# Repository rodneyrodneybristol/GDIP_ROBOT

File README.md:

# UWE GDIP 2022, GROUP 7D RESISTOR SORTING ROBOT

<b>How to assemble and run</b>
<br>
To install:
<br>
```
git clone https://github.com/rodneyrodneybristol/GDIP_ROBOT
```
<br>
or download the .zip repository directly
<br><br>
Install platform IO, to open the firmware files for the motherboard and ohm meter board. 
<br>
Firmware may take a little while to load and build initially if you do not already have the Pi Pico SDK and Arduino frameworks installed. 
<br>
Firmware can be loaded to the Pi Pico directly and the Atmega328p can be programmed using an AVR programmer or Arduino in ISP programmer mode.
<br><br>
to 3D print the conveoyr belt, simply load the provided STLs in to any chopper software. Best to print them vertically to avoid excessive infil.
<br><br>
2 x 5V supplies, with at least 2A each are required  to run this system, one which handles the mobo/servos/ohm meter etc and another for powering the conveoyrs NEMA17 stepper motor. 
<br><br>
Calibration offset for the Robot can be adjusted in the 
```
startAndCalibrateArm();
``` function within the mobo/mainboard main.cpp file. These will need to be set once when loading the system, in case any servos have serious offsets. This allows for more precise movements of the arm.
<br><br>

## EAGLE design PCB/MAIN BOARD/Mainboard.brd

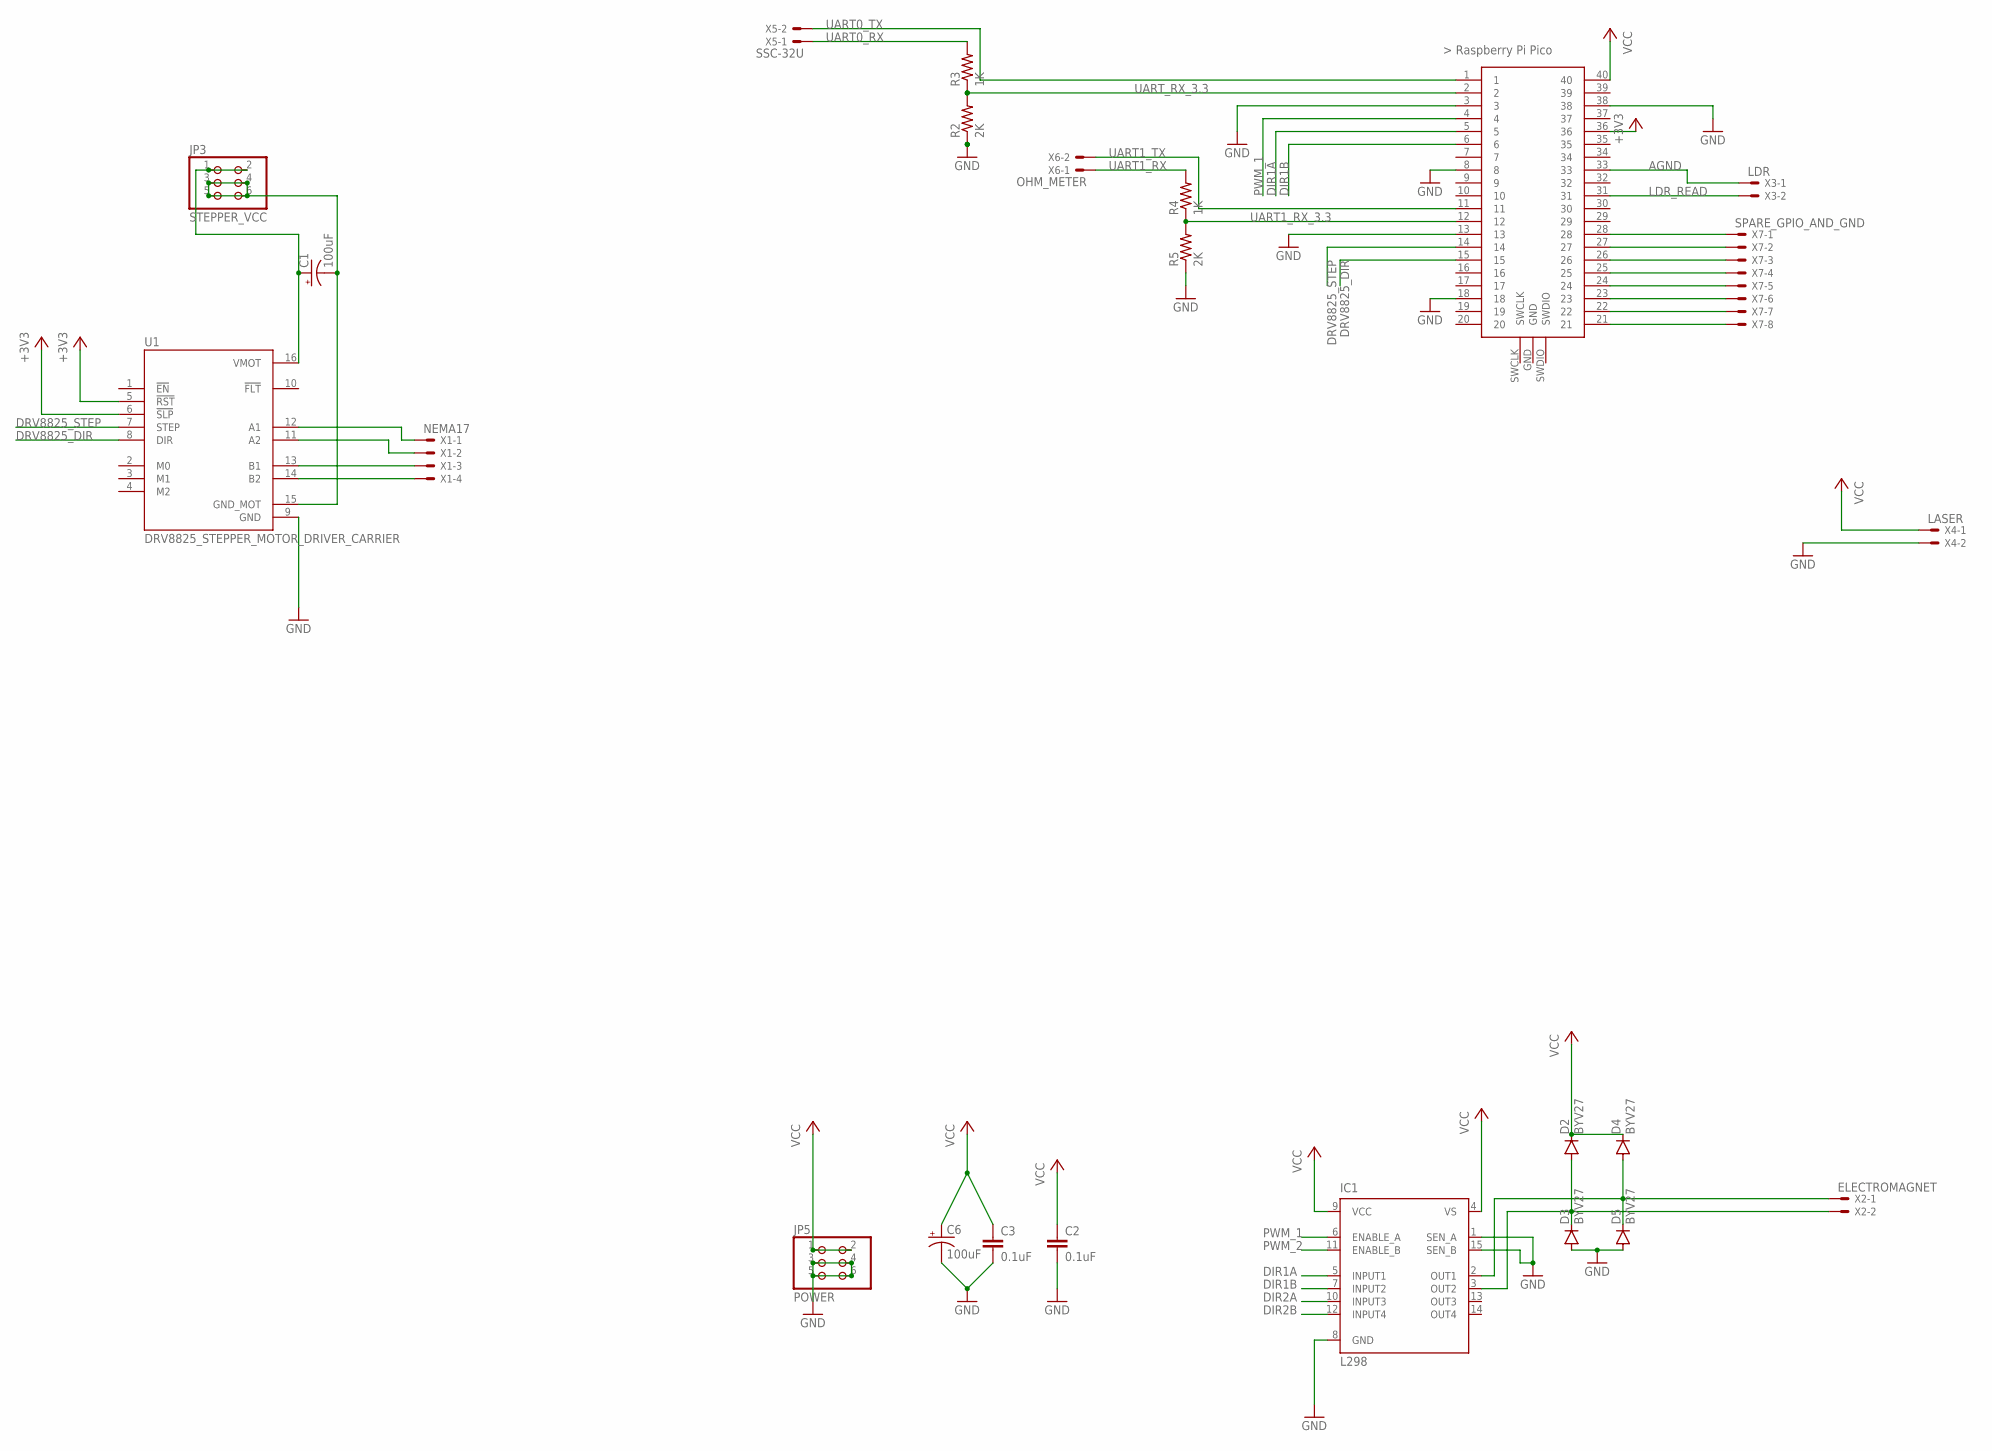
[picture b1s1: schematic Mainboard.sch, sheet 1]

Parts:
C1, C6: 100uF; CPOL-RADIAL-2.5MM-6.5MM
C2, C3: 0.1uF; 0603
D2, D3, D4, D5: BYV27; SOD57-10
IC1: L298; MULTIWATT-15
JP3: STEPPER_VCC; 2X03
JP5: POWER; 2X03
R2, R5: 2K; R0603
R3, R4: 1K; R0603
U1: DRV8825_STEPPER_MOTOR_DRIVER_CARRIER; IC_DRV8825_STEPPER_MOTOR_DRIVER_CARRIER
U$1: RASPBERRY-PI-PICO_W; FT_RASPBERRY-PI-PICO_TH
X1: NEMA17; 22-23-2041
X2: ELECTROMAGNET; 22-23-2021
X3: LDR; 22-23-2021
X4: LASER; 22-23-2021
X5: SSC-32U; 22-23-2021
X6: OHM_METER; 22-23-2021
X7: SPARE_GPIO_AND_GND; 22-23-2081

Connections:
+3V3: U1.5 (!RST), U1.6 (!SLP), U$1.36
+5V: C2.1, IC1.9 (VCC)
AGND: U$1.33, X3.1
DIR1A: IC1.5 (INPUT1), U$1.5
DIR1B: IC1.7 (INPUT2), U$1.6
DIR2A: IC1.10 (INPUT3)
DIR2B: IC1.12 (INPUT4)
DRV8825_DIR: U1.8 (DIR), U$1.15
DRV8825_STEP: U1.7 (STEP), U$1.14
GND: C2.2, C3.2, C6.2 (-), D3.A, D5.A, IC1.1 (SEN_A), IC1.8 (GND), IC1.15 (SEN_B), JP5.3, JP5.4, JP5.5, JP5.6, R2.1, R5.1, U1.9 (GND), U$1.3, U$1.8, U$1.13, U$1.18, U$1.38, X4.2
LDR_READ: U$1.31, X3.2
MOTOR_1_+: D4.A, D5.C, IC1.2 (OUT1), X2.1
MOTOR_1_-: D2.A, D3.C, IC1.3 (OUT2), X2.2
unnamed: C1.1 (+), JP3.1, JP3.2, U1.16 (VMOT)
unnamed: C1.2 (-), JP3.3, JP3.4, JP3.5, JP3.6, U1.15 (GND_MOT)
unnamed: U1.12 (A1), X1.1
unnamed: U1.11 (A2), X1.2
unnamed: U1.13 (B1), X1.3
unnamed: U1.14 (B2), X1.4
unnamed: U$1.21, X7.8
unnamed: U$1.22, X7.7
unnamed: U$1.25, X7.4
unnamed: U$1.23, X7.6
unnamed: U$1.24, X7.5
unnamed: U$1.26, X7.3
unnamed: U$1.27, X7.2
unnamed: U$1.28, X7.1
PWM_1: IC1.6 (ENABLE_A), U$1.4
PWM_2: IC1.11 (ENABLE_B)
UART0_RX: R3.2, X5.1
UART0_TX: U$1.1, X5.2
UART1_RX: R4.2, X6.1
UART1_RX_3.3: R4.1, R5.2, U$1.12
UART1_TX: U$1.11, X6.2
UART_RX_3.3: R2.2, R3.1, U$1.2
VCC: C3.1, C6.1 (+), D2.C, D4.C, IC1.4 (VS), JP5.1, JP5.2, U$1.40, X4.1

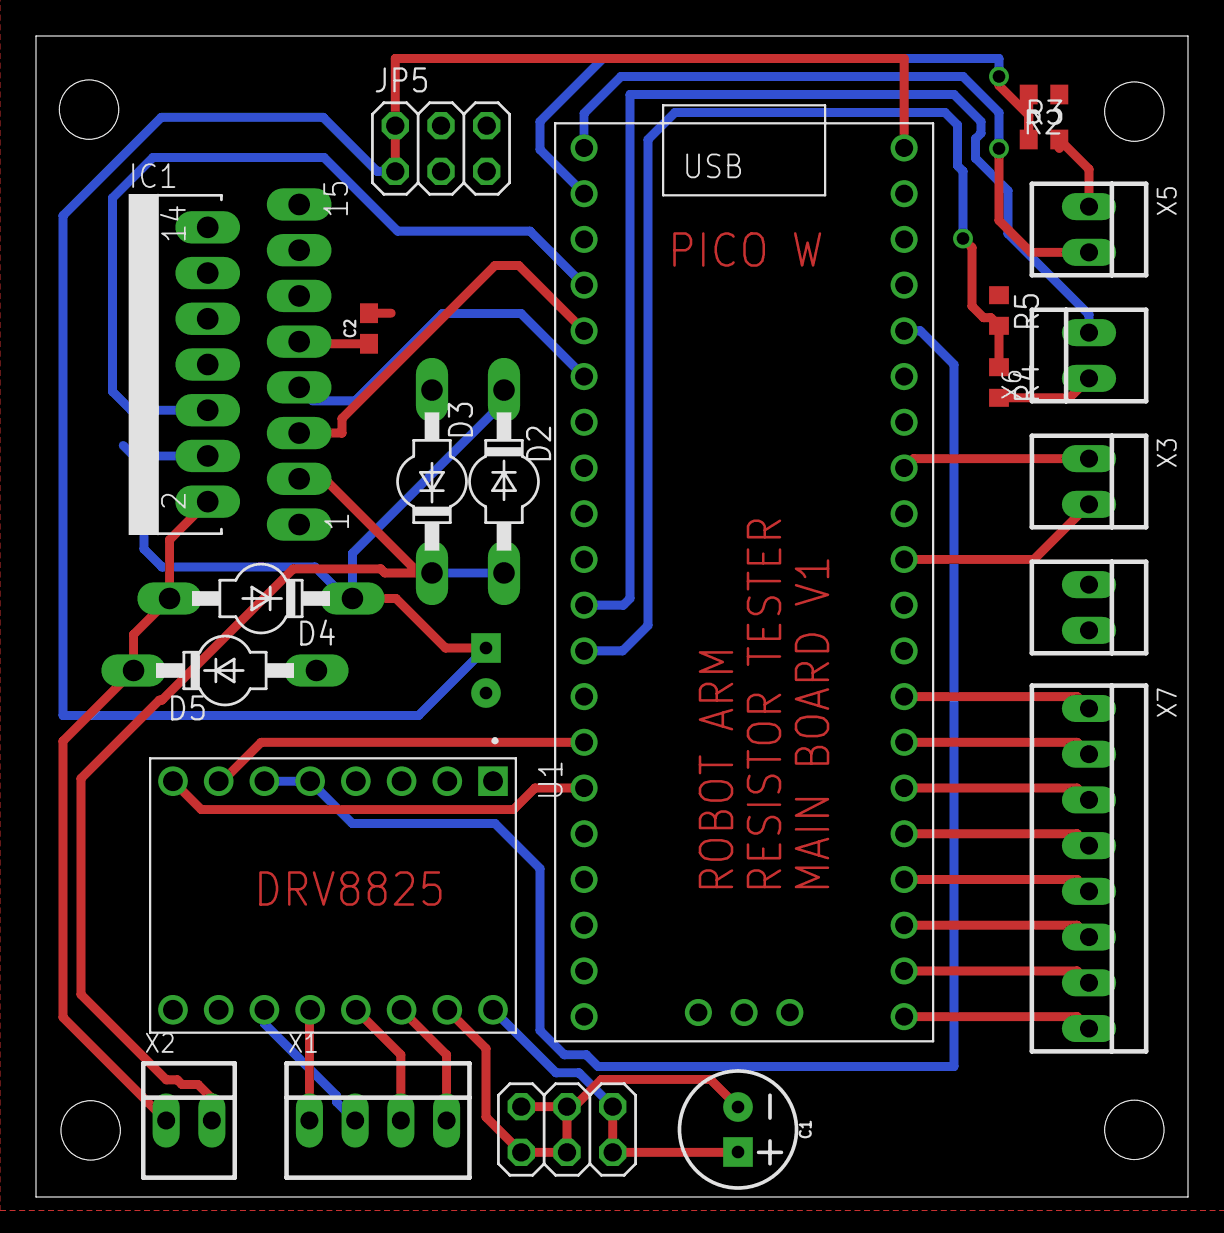
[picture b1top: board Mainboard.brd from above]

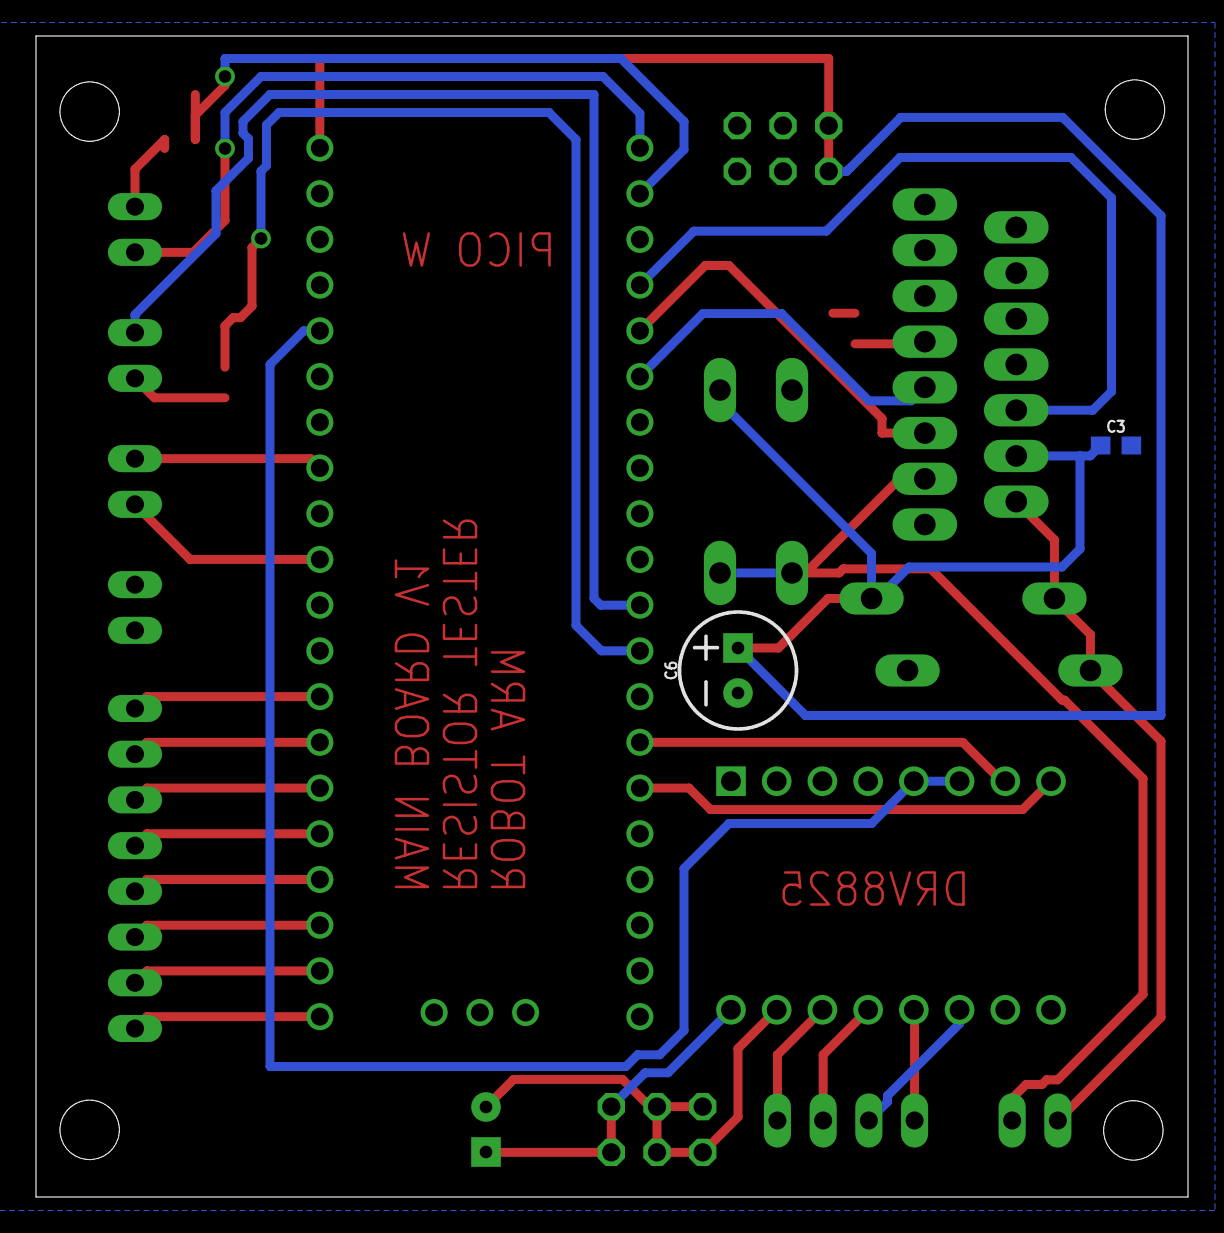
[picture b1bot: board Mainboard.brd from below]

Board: 2 copper layers, 64.0 x 64.5 mm, 24 parts (2 on the bottom side), 33 nets.

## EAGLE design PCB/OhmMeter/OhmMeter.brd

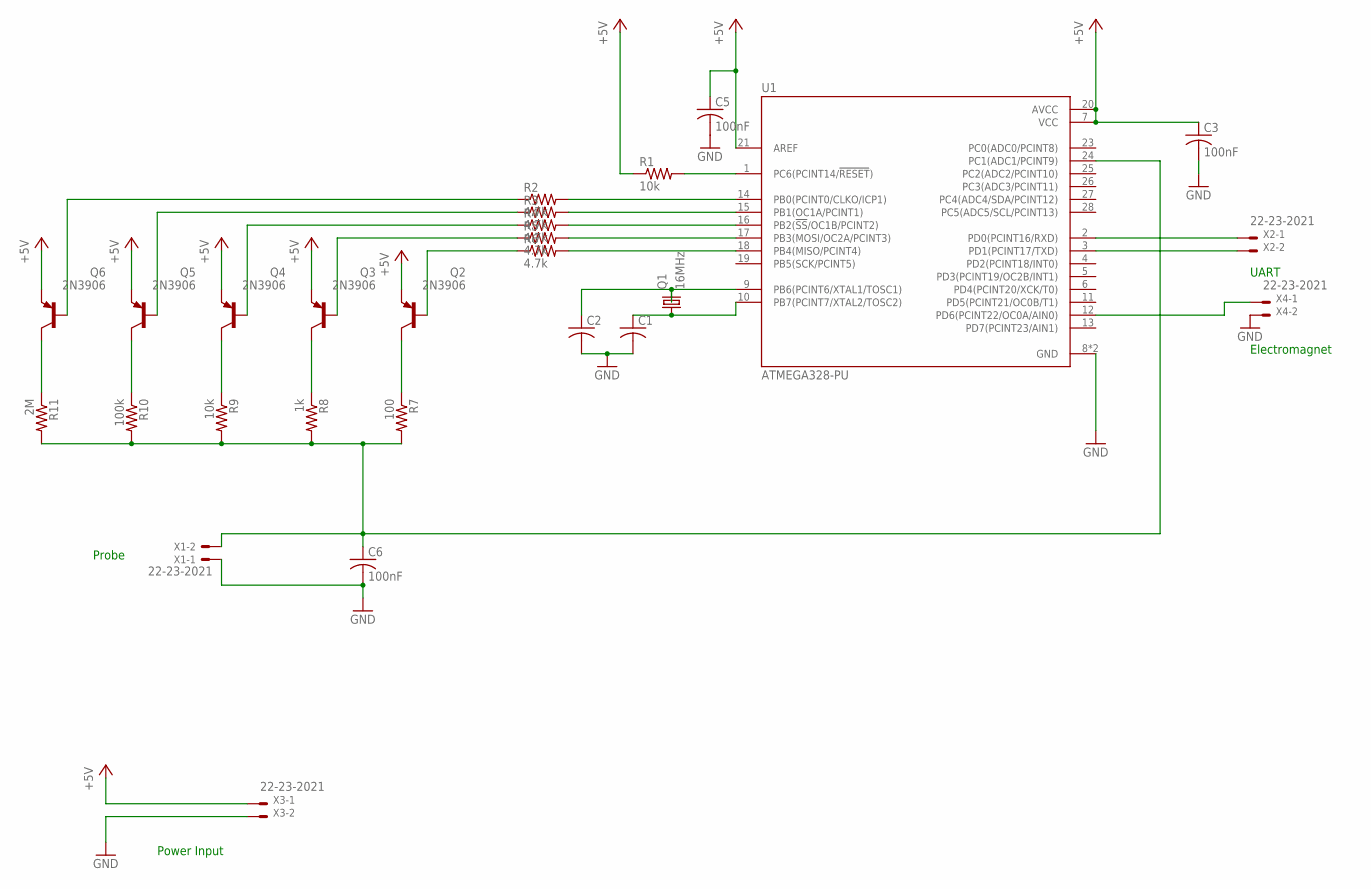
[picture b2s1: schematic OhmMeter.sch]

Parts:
C1, C2: C-US025-024X044; C025-024X044
C3, C5, C6: 100nF; C025-024X044
Q1: 16MHz; HC49/S
Q2, Q3, Q4, Q5, Q6: 2N3906; TO92
R1, R9: 10k; 0204/5
R2, R3, R4, R5, R6: 4.7k; 0204/5
R7: 100; 0204/5
R8: 1k; 0204/5
R10: 100k; 0204/5
R11: 2M; 0204/5
U1: ATMEGA328-PU; DIP787W46P254L3467H508Q28
X1, X2, X3, X4: 22-23-2021

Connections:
+5V: C3.1, C5.1, Q2.3 (E), Q3.3 (E), Q4.3 (E), Q5.3 (E), Q6.3 (E), R1.1, U1.7 (VCC), U1.20 (AVCC), U1.21 (AREF), X3.1
GND: C1.2, C2.2, C3.2, C5.2, C6.2, U1.8 (GND), U1.22 (GND), X1.1, X3.2, X4.2
unnamed: C2.1, Q1.2, U1.9 (PB6(PCINT6/XTAL1/TOSC1))
unnamed: C1.1, Q1.1, U1.10 (PB7(PCINT7/XTAL2/TOSC2))
unnamed: R6.2, U1.18 (PB4(MISO/PCINT4))
unnamed: R5.2, U1.17 (PB3(MOSI/OC2A/PCINT3))
unnamed: R4.2, U1.16 (PB2(!SS!/OC1B/PCINT2))
unnamed: R3.2, U1.15 (PB1(OC1A/PCINT1))
unnamed: R2.2, U1.14 (PB0(PCINT0/CLKO/ICP1))
unnamed: R1.2, U1.1 (PC6(PCINT14/!RESET!))
unnamed: Q2.2 (B), R6.1
unnamed: Q3.2 (B), R5.1
unnamed: Q4.2 (B), R4.1
unnamed: Q5.2 (B), R3.1
unnamed: Q2.1 (C), R7.1
unnamed: Q6.2 (B), R2.1
unnamed: Q3.1 (C), R8.1
unnamed: Q4.1 (C), R9.1
unnamed: Q5.1 (C), R10.1
unnamed: Q6.1 (C), R11.1
unnamed: C6.1, R7.2, R8.2, R9.2, R10.2, R11.2, U1.24 (PC1(ADC1/PCINT9)), X1.2
unnamed: U1.2 (PD0(PCINT16/RXD)), X2.1
unnamed: U1.3 (PD1(PCINT17/TXD)), X2.2
unnamed: U1.12 (PD6(PCINT22/OC0A/AIN0)), X4.1

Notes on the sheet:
Probe
UART
Power Input
Electromagnet

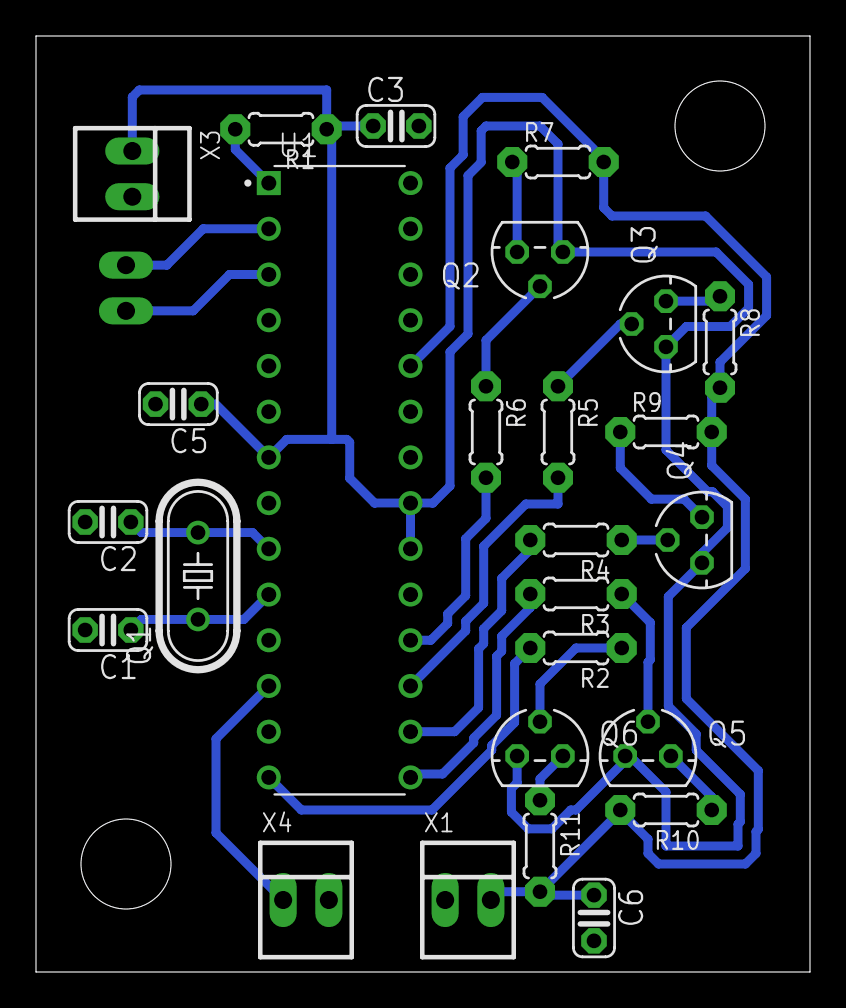
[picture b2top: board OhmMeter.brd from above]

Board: 2 copper layers, 43.0 x 52.0 mm, 27 parts (1 on the bottom side), 24 nets.

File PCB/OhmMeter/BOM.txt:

Partlist exported from C:/Users/jimbo/Documents/GitHub/GDIP_ROBOT/PCB/OhmMeter/OhmMeter.sch at 25/11/2022 05:41

Qty Value        Device          Package                   Parts              Description                                                                                      AVAILABILITY DESCRIPTION                                                                    MF                   MP           MPN        OC_FARNELL OC_NEWARK PACKAGE                     POPULARITY PRICE PURCHASE-URL                                                 
2                C-US025-024X044 C025-024X044              C1, C2             CAPACITOR, American symbol                                                                                                                                                                                                                                                                                                                                               
1   100          R-US_0204/5     0204/5                    R7                 RESISTOR, American symbol                                                                                                                                                                                                                                                                                                                                                
1   100k         R-US_0204/5     0204/5                    R10                RESISTOR, American symbol                                                                                                                                                                                                                                                                                                                                                
3   100nF        C-US025-024X044 C025-024X044              C3, C5, C6         CAPACITOR, American symbol                                                                                                                                                                                                                                                                                                                                               
2   10k          R-US_0204/5     0204/5                    R1, R9             RESISTOR, American symbol                                                                                                                                                                                                                                                                                                                                                
1   16MHz        CRYSTALHC49S    HC49/S                    Q1                 CRYSTAL                                                                                                                                                                                                                                   1667008    unknown                                                                                                             
1   1k           R-US_0204/5     0204/5                    R8                 RESISTOR, American symbol                                                                                                                                                                                                                                                                                                                                                
4   22-23-2021   22-23-2021      22-23-2021                X1, X2, X3, X4     .100" (2.54mm) Center Header - 2 Pin                                                                                                                                                         MOLEX                             22-23-2021 1462926    25C3832                               40                                                                            
1   2M           R-US_0204/5     0204/5                    R11                RESISTOR, American symbol                                                                                                                                                                                                                                                                                                                                                
5   2N3906       2N3906          TO92                      Q2, Q3, Q4, Q5, Q6 PNP Transistor                                                                                                                                                                                                                                                                             11                                                                            
5   4.7k         R-US_0204/5     0204/5                    R2, R3, R4, R5, R6 RESISTOR, American symbol                                                                                                                                                                                                                                                                                                                                                
1   ATMEGA328-PU ATMEGA328-PU    DIP787W46P254L3467H508Q28 U1                 AVR AVR® ATmega Microcontroller IC 8-Bit 20MHz 32KB (16K x 16) FLASH 28-PDIP  Check availability In Stock      AVR AVR® ATmega Microcontroller IC 8-Bit 20MHz 32KB (16K x 16) FLASH 28-PDIP  Microchip Technology ATMEGA328-PU                                 DIP-28 Microchip Technology            None  https://pricing.snapeda.com/search/part/ATMEGA328-PU/?ref=eda

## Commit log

2022-10-24 Add files via upload
    This is the work breakdown structure for the project
2022-10-26 test
    teste
2022-10-28 Create Links to Work breakdown structure and Node diagram
2022-11-02 Add files via upload
    These are the Initial gripper design, the indent on the tip is for the metallic tape/strip for contacts, and the electro magnet can be mounted in the free space in between the grippers
2022-11-09 Preliminary Gantt Chart
    Have done basic resource allocation (staffing), further allocation should be done once materials requirements and costings are defined.
2022-11-09 Clean up
2022-11-21 Create Link to my onedrive file - Report is in here
    This is the link to my one drive file which has a bunch of stuff mainly the start of the report
2022-11-25 Firmware
2022-11-25 CleanUp
2022-11-25 Initial meter firmware
2022-11-25 PCB SCH and BRD
2022-11-28 Firmware Update
    Confirmed working hardware and code using combination of electromagnet and ohm meter on prototype gripper
2022-11-29 Add files via upload
    Updated Team Structure Flow diagram with Emre
2022-11-30 Add files via upload
    By John
2022-11-30 Fusion files added
2022-12-01 Meeting minutes for 30th Nov
2022-12-04 Emre stakeholder analysis
2022-12-05 More PM stuff
2022-12-07 Revert "Add files via upload"
2022-12-10 Added kinematics C script and some other stuff
    Kinematics script, written for now as a C program that outputs the desired codes for the SSC-32 based on X,Y,Z positions.
2022-12-22 I will update the report on here but we should write it using the onedrive link
2023-01-06 Update Gripper
2023-01-09 Exported some of the earlier gripper iterations
2023-01-10 Firmware cleanup and other stuff
2023-01-10 More images added
2023-01-13 Renames Risk analysis to risk mitigation
2023-01-13 Addition of photos and videos to github
2023-01-13 Move files

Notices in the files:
parts and their libraries:
SparkFun-Capacitors: Licensing: Creative Commons ShareAlike 4.0 International - https://creativecommons.org/licenses/by-sa/4.0
